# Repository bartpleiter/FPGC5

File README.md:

# FPGC5

My big project, basically started in July 2019 as FPGC3 (versions 1 and 2 do not count). Project exists to learn more about the fundamentals of computers and to improve my Verilog skills, while also designing my own "environment" (PCB, Compilers, OS, etc.) around it.

FPGC is a completely self designed computer, implemented in an EP4CE15 FPGA.

[Project Wiki](https://www.b4rt.nl/fpgc5/) (not fully up to date, but contains a lot of info)

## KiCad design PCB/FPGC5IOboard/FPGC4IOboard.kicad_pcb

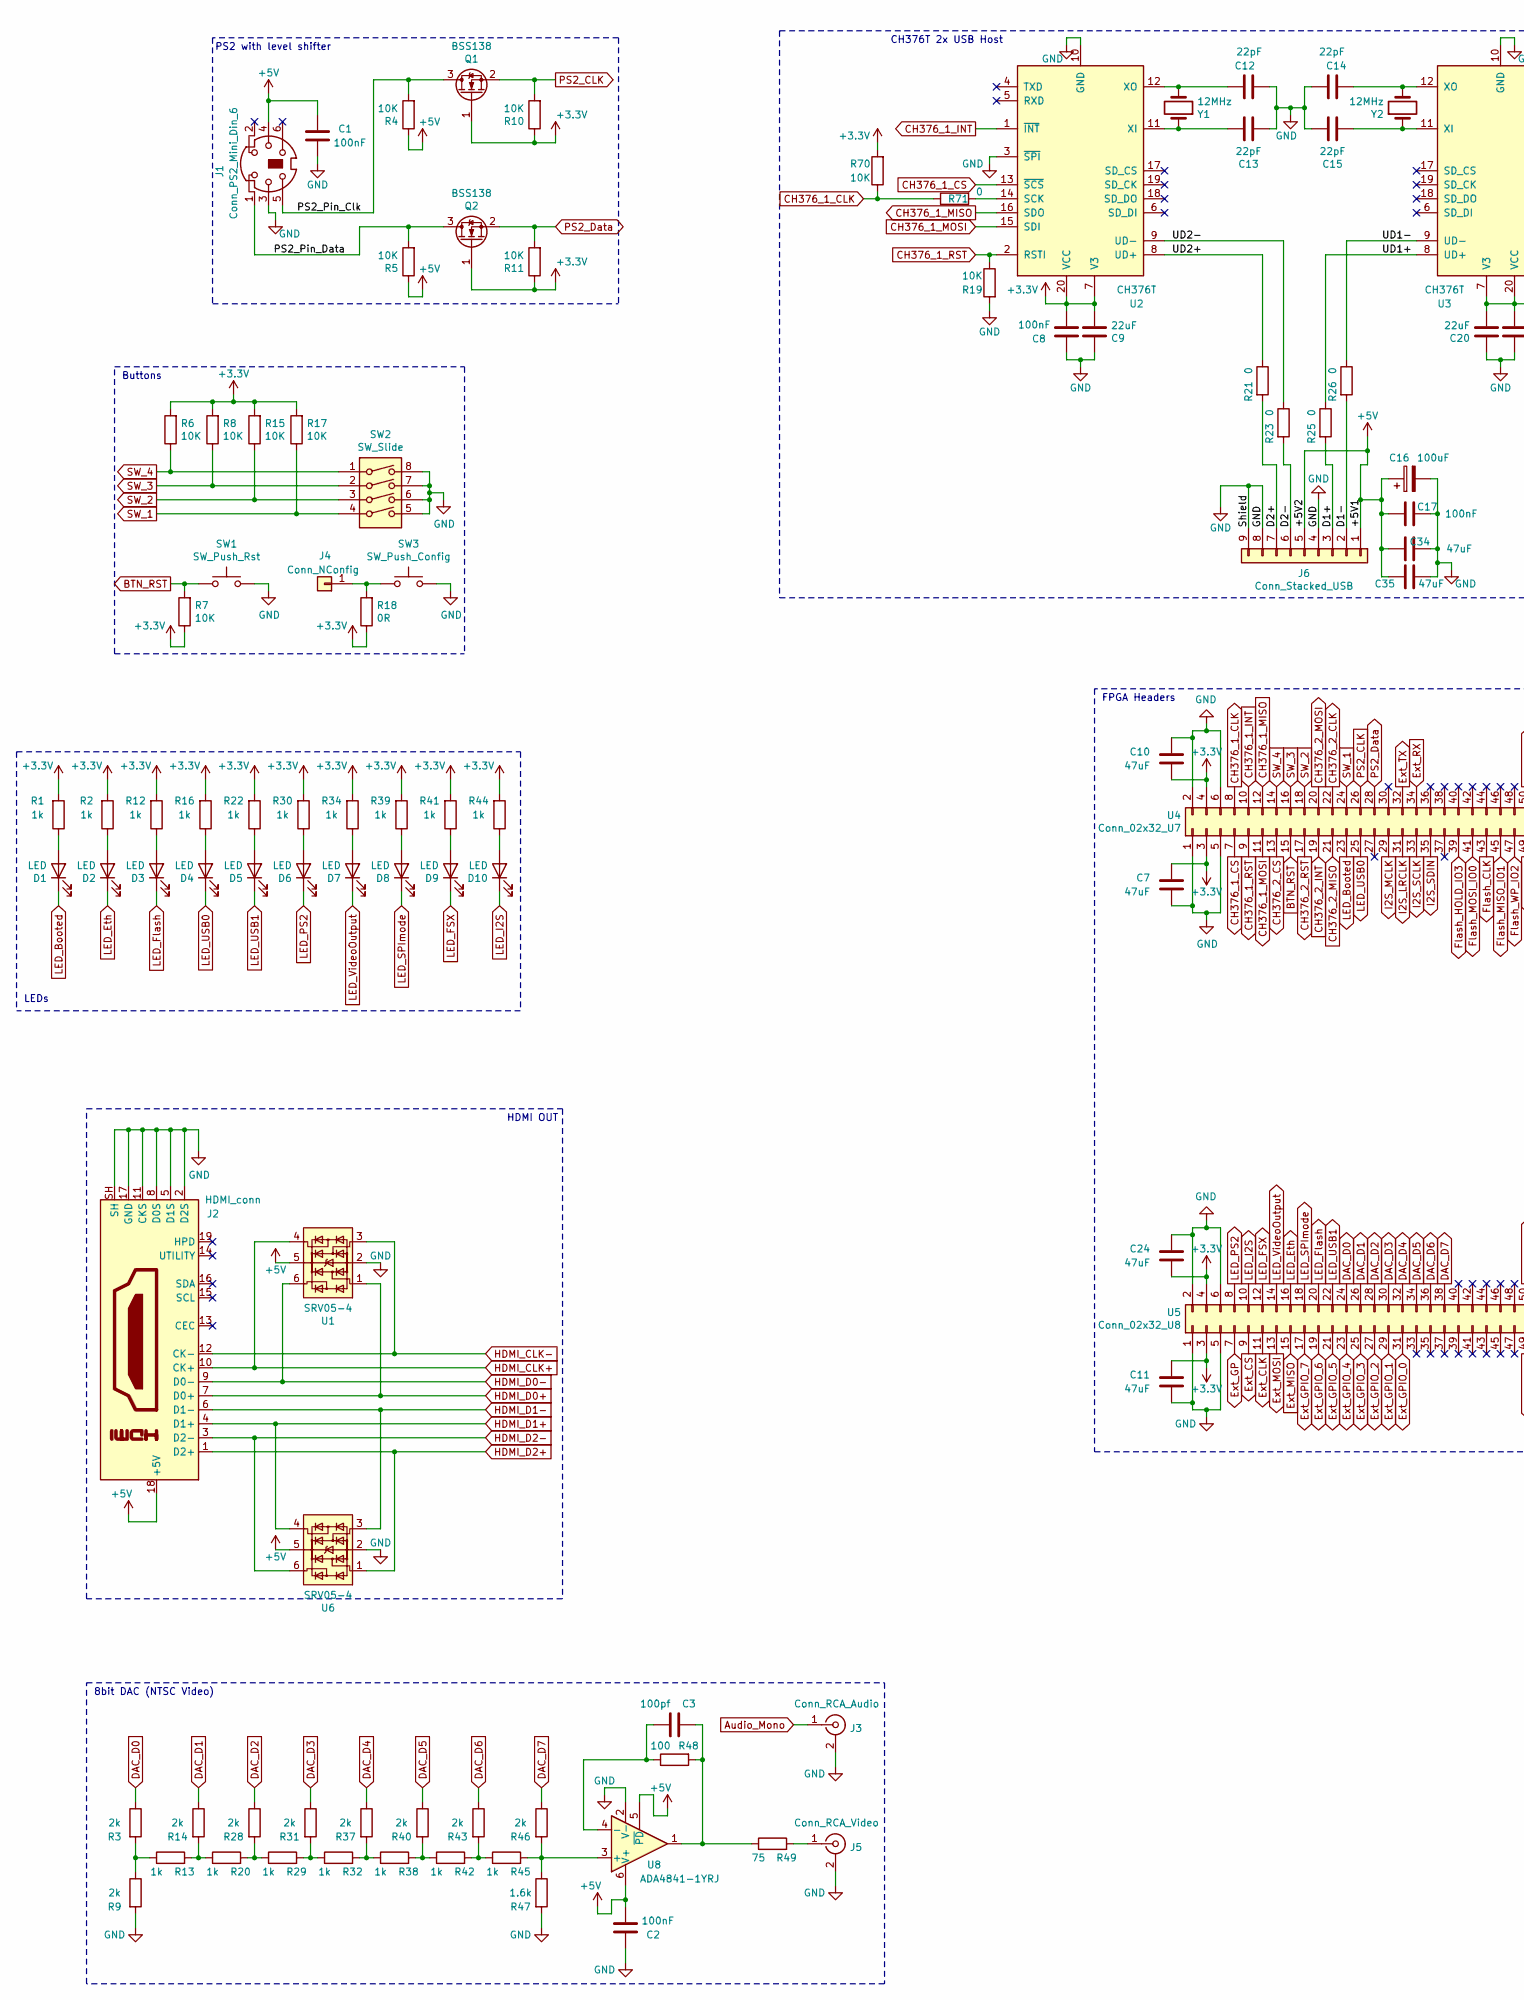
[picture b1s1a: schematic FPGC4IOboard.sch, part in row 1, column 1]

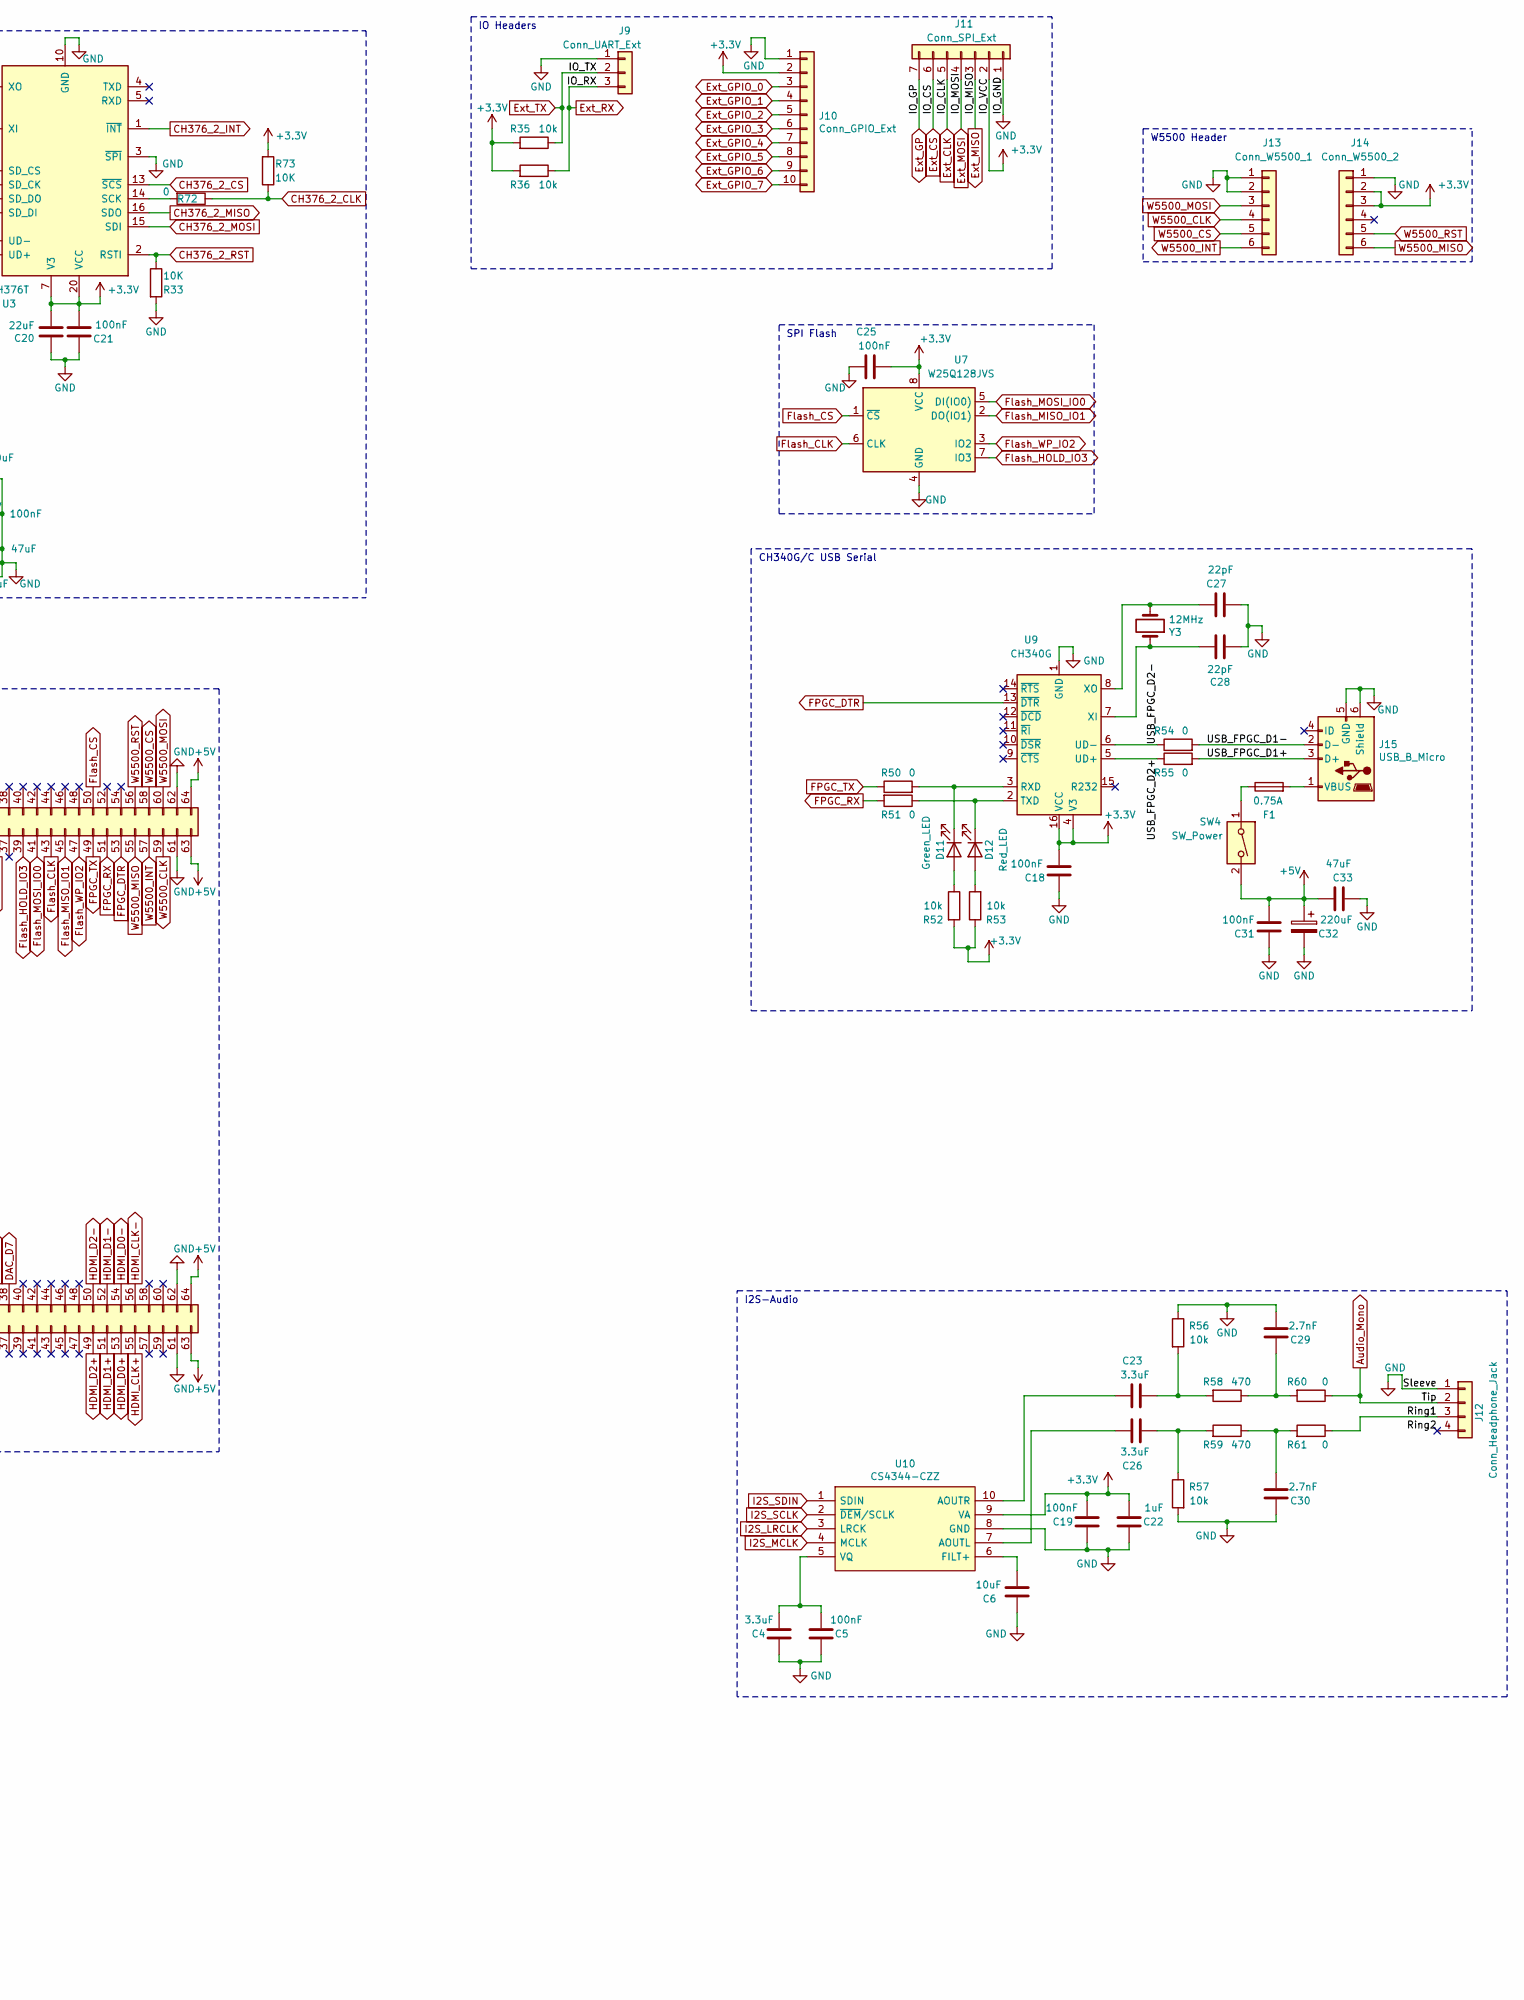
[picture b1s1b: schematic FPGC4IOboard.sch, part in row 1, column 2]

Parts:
C1, C2, C5, C8, C17, C18, C19, C21, C25, C31: 100nF; C_0805_2012Metric_Pad1.18x1.45mm_HandSolder
C3: 100pf; C_0805_2012Metric_Pad1.18x1.45mm_HandSolder
C4, C23, C26: 3.3uF; C_0805_2012Metric_Pad1.18x1.45mm_HandSolder
C6: 10uF; C_0805_2012Metric_Pad1.18x1.45mm_HandSolder
C7, C10, C11, C24, C33, C34, C35: 47uF; C_0805_2012Metric_Pad1.18x1.45mm_HandSolder
C9, C20: 22uF; C_0805_2012Metric_Pad1.18x1.45mm_HandSolder
C12, C13, C14, C15, C27, C28: 22pF; C_0805_2012Metric_Pad1.18x1.45mm_HandSolder
C16: 100uF; CP_Radial_D4.0mm_P2.00mm
C22: 1uF; C_0805_2012Metric_Pad1.18x1.45mm_HandSolder
C29, C30: 2.7nF; C_0805_2012Metric_Pad1.18x1.45mm_HandSolder
C32: 220uF; CP_Radial_D5.0mm_P2.00mm
D1, D2, D3, D4, D5, D6, D7, D8, D9, D10: LED; LED_0805_2012Metric_Pad1.15x1.40mm_HandSolder
D11: Green_LED; LED_0805_2012Metric_Pad1.15x1.40mm_HandSolder
D12: Red_LED; LED_0805_2012Metric_Pad1.15x1.40mm_HandSolder
F1: 0.75A; Fuse_1812
J1: Conn_PS2_Mini_Din_6; PS2
J2: HDMI_conn; HDMI_connector_19
J3: Conn_RCA_Audio; CUI_RCJ-013-Min
J4: Conn_NConfig; PinHeader_1x01_P2.54mm_Vertical
J5: Conn_RCA_Video; CUI_RCJ-013-Min
J6: Conn_Stacked_USB; USB_A_Wuerth_61400826021_Horizontal_Stacked
J9: Conn_UART_Ext; PinSocket_1x03_P2.54mm_Vertical
J10: Conn_GPIO_Ext; PinSocket_1x10_P2.54mm_Vertical
J11: Conn_SPI_Ext; PinSocket_1x07_P2.54mm_Vertical
J12: Conn_Headphone_Jack; TRRS-PJ-320A
J13: Conn_W5500_1; PinSocket_1x06_P2.54mm_Vertical
J14: Conn_W5500_2; PinSocket_1x06_P2.54mm_Vertical
J15: USB_B_Micro; MicroUSB_G30
Q1, Q2: BSS138; SOT-23
R1, R2, R12, R13, R16, R20, R22, R29, R30, R32, R34, R38, R39, R41, R42, R44, R45: 1k; R_0805_2012Metric_Pad1.20x1.40mm_HandSolder
R3, R9, R14, R28, R31, R37, R40, R43, R46: 2k; R_0805_2012Metric_Pad1.20x1.40mm_HandSolder
R4, R5, R6, R7, R8, R10, R11, R15, R17, R19, R33, R70, R73: 10K; R_0805_2012Metric_Pad1.20x1.40mm_HandSolder
R18: 0R; R_0805_2012Metric_Pad1.20x1.40mm_HandSolder
R21, R23, R25, R26, R50, R51, R54, R55, R60, R61, R71, R72: 0; R_0805_2012Metric_Pad1.20x1.40mm_HandSolder
R35, R36, R52, R53, R56, R57: 10k; R_0805_2012Metric_Pad1.20x1.40mm_HandSolder
R47: 1.6k; R_0805_2012Metric_Pad1.20x1.40mm_HandSolder
R48: 100; R_0805_2012Metric_Pad1.20x1.40mm_HandSolder
R49: 75; R_0805_2012Metric_Pad1.20x1.40mm_HandSolder
R58, R59: 470; R_0805_2012Metric_Pad1.20x1.40mm_HandSolder
SW1: SW_Push_Rst; SW_Tactile_SPST_Angled_PTS645Vx39-2LFS
SW2: SW_Slide; SW_DIP_SPSTx04_Slide_6.7x11.72mm_W8.61mm_P2.54mm_LowProfile
SW3: SW_Push_Config; SW_Tactile_SPST_Angled_PTS645Vx39-2LFS
SW4: SW_Power; SS12D06
U1, U6: SRV05-4; SOT-23-6
U2, U3: CH376T; SSOP-20_5.3x7.2mm_P0.65mm
U4: Conn_02x32_U7; PinHeader_2x32_P2.54mm_Vertical
U5: Conn_02x32_U8; PinHeader_2x32_P2.54mm_Vertical
U7: W25Q128JVS; SOIC-8_5.23x5.23mm_P1.27mm
U8: ADA4841-1YRJ; SOT-23-6
U9: CH340G; SOIC-16_3.9x9.9mm_P1.27mm
U10: CS4344-CZZ; SOP50P490X110-10N; Manufacturer_Part_Number CS4344-CZZ; Mouser Part Number 777-CS4344-CZZ
Y1, Y2, Y3: 12MHz; Crystal_HC49-4H_Vertical

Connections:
+3V3: C7.1, C8.2, C9.2, C10.2, C11.1, C18.2, C19.1, C20.2, C21.2, C22.1, C24.2, C25.2, J10.2, J11.2, J14.2, J14.3, Q1.1 (G), Q2.1 (G), R1.2, R2.2, R6.2, R7.1, R8.2, R10.1, R11.1, R12.2, R15.2, R16.2, R17.2, R18.1, R22.2, R30.2, R34.2, R35.2, R36.2, R39.2, R41.2, R44.2, R52.2, R53.1, R70.2, R73.2, U2.7 (V3), U2.20 (VCC), U3.7 (V3), U3.20 (VCC), U4.3, U4.4, U5.3, U5.4, U7.8 (VCC), U9.4 (V3), U9.16 (VCC), U10.9 (VA)
+5V: C1.1, C2.1, C16.1, C17.2, C31.2, C32.1, C33.2, C34.1, C35.1, J1.4, J2.18 (+5V), J6.1, J6.5, R4.1, R5.1, SW4.2, U1.5, U4.63, U4.64, U5.63, U5.64, U6.5, U8.5 (~PD), U8.6 (V+)
/D1+: J6.3, R25.2
/D1-: J6.2, R26.2
/D2+: J6.7, R21.2
/D2-: J6.6, R23.2
/PS2_Pin_Clk: J1.5, Q1.3 (D), R4.2
/PS2_Pin_Data: J1.1, Q2.3 (D), R5.2
/Ring1: J12.3, R61.1
/Ring2: J12.4
/UD1+: R25.1, U3.8 (UD+)
/UD1-: R26.1, U3.9 (UD-)
/UD2+: R21.1, U2.8 (UD+)
/UD2-: R23.1, U2.9 (UD-)
/USB_FPGC_D1+: J15.3 (D+), R55.2
/USB_FPGC_D1-: J15.2 (D-), R54.2
/USB_FPGC_D2+: R55.1, U9.5 (UD+)
/USB_FPGC_D2-: R54.1, U9.6 (UD-)
Audio_Mono: J3.1 (In), J12.2, R60.1
BTN_RST: R7.2, SW1.1, U4.15
CH376_1_CLK: R70.1, R71.1, U4.8
CH376_1_CS: U2.13 (~SCS), U4.7
CH376_1_INT: U2.1 (~INT~), U4.10
CH376_1_MISO: U2.16 (SDO), U4.12
CH376_1_MOSI: U2.15 (SDI), U4.11
CH376_1_RST: R19.1, U2.2 (RSTI), U4.9
CH376_2_CLK: R72.1, R73.1, U4.22
CH376_2_CS: U3.13 (~SCS), U4.13
CH376_2_INT: U3.1 (~INT~), U4.19
CH376_2_MISO: U3.16 (SDO), U4.21
CH376_2_MOSI: U3.15 (SDI), U4.20
CH376_2_RST: R33.1, U3.2 (RSTI), U4.17
DAC_D0: R3.1, U5.24
DAC_D1: R14.1, U5.26
DAC_D2: R28.1, U5.28
DAC_D3: R31.1, U5.30
DAC_D4: R37.1, U5.32
DAC_D5: R40.1, U5.34
DAC_D6: R43.1, U5.36
DAC_D7: R46.1, U5.38
Ext_CLK: J11.5, U5.11
Ext_CS: J11.6, U5.9
Ext_GP: J11.7, U5.7
Ext_GPIO_0: J10.3, U5.31
Ext_GPIO_1: J10.4, U5.29
Ext_GPIO_2: J10.5, U5.27
Ext_GPIO_3: J10.6, U5.25
Ext_GPIO_4: J10.7, U5.23
Ext_GPIO_5: J10.8, U5.21
Ext_GPIO_6: J10.9, U5.19
Ext_GPIO_7: J10.10, U5.17
Ext_MISO: J11.3, U5.15
Ext_MOSI: J11.4, U5.13
Ext_RX: J9.3, R36.1, U4.34
Ext_TX: J9.2, R35.1, U4.32
FPGC_DTR: U4.53, U9.13 (~DTR)
FPGC_RX: R51.2, U4.51
FPGC_TX: R50.1, U4.49
Flash_CLK: U4.43, U7.6 (CLK)
Flash_CS: U4.50, U7.1 (~CS)
Flash_HOLD_IO3: U4.39, U7.7 (IO3)
Flash_MISO_IO1: U4.45, U7.2 (DO(IO1))
Flash_MOSI_IO0: U4.41, U7.5 (DI(IO0))
Flash_WP_IO2: U4.47, U7.3 (IO2)
GND: C1.2, C2.2, C4.2, C5.2, C6.2, C7.2, C8.1, C9.1, C10.1, C11.2, C12.2, C13.1, C14.2, C15.1, C16.2, C17.1, C18.1, C19.2, C20.1, C21.1, C22.2, C24.1, C25.1, C27.2, C28.1, C29.1, C30.2, C31.1, C32.2, C33.1, C34.2, C35.2, J1.3, J2.2 (D2S), J2.5 (D1S), J2.8 (D0S), J2.11 (CKS), J2.17 (GND), J2.SH, J3.2 (Ext), J5.2 (Ext), J6.4, J6.8, J6.9, J9.1, J10.1, J11.1, J12.1, J13.1, J13.2, J14.1, J15.5 (GND), J15.6 (Shield), R9.2, R19.2, R33.2, R47.2, R56.1, R57.2, SW1.2, SW2.5, SW2.6, SW2.7, SW2.8, SW3.2, SW4.4, U1.2, U2.3 (~SPI~), U2.10 (GND), U3.3 (~SPI~), U3.10 (GND), U4.1, U4.2, U4.5, U4.6, U4.61, U4.62, U5.1, U5.2, U5.5, U5.6, U5.61, U5.62, U6.2, U7.4 (GND), U8.2 (V-), U9.1 (GND), U10.8 (GND)
HDMI_CLK+: J2.10 (CK+), U1.4, U5.55
HDMI_CLK-: J2.12 (CK-), U1.3, U5.56
HDMI_D0+: J2.7 (D0+), U1.1, U5.53
HDMI_D0-: J2.9 (D0-), U1.6, U5.54
HDMI_D1+: J2.4 (D1+), U5.51, U6.4
HDMI_D1-: J2.6 (D1-), U5.52, U6.3
HDMI_D2+: J2.1 (D2+), U5.49, U6.1
HDMI_D2-: J2.3 (D2-), U5.50, U6.6
I2S_LRCLK: U4.31, U10.3 (LRCK)
I2S_MCLK: U4.29, U10.4 (MCLK)
I2S_SCLK: U4.33, U10.2 (~DEM~/SCLK)
I2S_SDIN: U4.35, U10.1 (SDIN)
LED_Booted: D1.1 (K), U4.23
LED_Eth: D2.1 (K), U5.16
LED_FSX: D9.1 (K), U5.12
LED_Flash: D3.1 (K), U5.20
LED_I2S: D10.1 (K), U5.10
LED_PS2: D6.1 (K), U5.8
LED_SPImode: D8.1 (K), U5.18
LED_USB0: D4.1 (K), U4.25
LED_USB1: D5.1 (K), U5.22
LED_VideoOutput: D7.1 (K), U5.14
unnamed: C3.1, R48.2, R49.1, U8.1
unnamed: C3.2, R48.1, U8.4 (-)
unnamed: C4.1, C5.1, U10.5 (VQ)
unnamed: C6.1, U10.6 (FILT+)
unnamed: C12.1, U2.12 (XO), Y1.2
unnamed: C13.2, U2.11 (XI), Y1.1
unnamed: C14.1, U3.12 (XO), Y2.2
unnamed: C15.2, U3.11 (XI), Y2.1
unnamed: C23.1, U10.10 (AOUTR)
unnamed: C23.2, R56.2, R58.2
unnamed: C26.1, U10.7 (AOUTL)
unnamed: C26.2, R57.1, R59.2
unnamed: C27.1, U9.8 (XO), Y3.2
unnamed: C28.2, U9.7 (XI), Y3.1
unnamed: C29.2, R58.1, R60.2
unnamed: C30.1, R59.1, R61.2
unnamed: D1.2 (A), R1.1
unnamed: D2.2 (A), R2.1
unnamed: D3.2 (A), R12.1
unnamed: D4.2 (A), R16.1
unnamed: D5.2 (A), R22.1
unnamed: D6.2 (A), R30.1
unnamed: D7.2 (A), R34.1
unnamed: D8.2 (A), R39.1
unnamed: D9.2 (A), R41.1
unnamed: D10.2 (A), R44.1
unnamed: D11.1 (K), R50.2, U9.3 (RXD)
unnamed: D11.2 (A), R52.1
unnamed: D12.1 (K), R51.1, U9.2 (TXD)
unnamed: D12.2 (A), R53.2
unnamed: F1.1, SW4.1
unnamed: F1.2, J15.1 (VBUS)
unnamed: J4.1, R18.2, SW3.1
unnamed: J5.1 (In), R49.2
unnamed: R3.2, R9.1, R13.1
unnamed: R13.2, R14.2, R20.1
unnamed: R20.2, R28.2, R29.1
unnamed: R29.2, R31.2, R32.1
unnamed: R32.2, R37.2, R38.1
unnamed: R38.2, R40.2, R42.1
unnamed: R42.2, R43.2, R45.1
unnamed: R45.2, R46.2, R47.1, U8.3 (+)
unnamed: R71.2, U2.14 (SCK)
unnamed: R72.2, U3.14 (SCK)
PS2_CLK: Q1.2 (S), R10.2, U4.26
PS2_Data: Q2.2 (S), R11.2, U4.28
SW_1: R17.1, SW2.4, U4.24
SW_2: R15.1, SW2.3, U4.18
SW_3: R8.1, SW2.2, U4.16
SW_4: R6.1, SW2.1, U4.14
W5500_CLK: J13.4, U4.59
W5500_CS: J13.5, U4.58
W5500_INT: J13.6, U4.57
W5500_MISO: J14.6, U4.55
W5500_MOSI: J13.3, U4.60
W5500_RST: J14.5, U4.56

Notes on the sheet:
CH340G/C USB Serial
IO Headers
PS2 with level shifter
CH376T 2x USB Host
I2S-Audio
SPI Flash
W5500 Header
Buttons
FPGA Headers
LEDs
HDMI OUT
8bit DAC (NTSC Video)

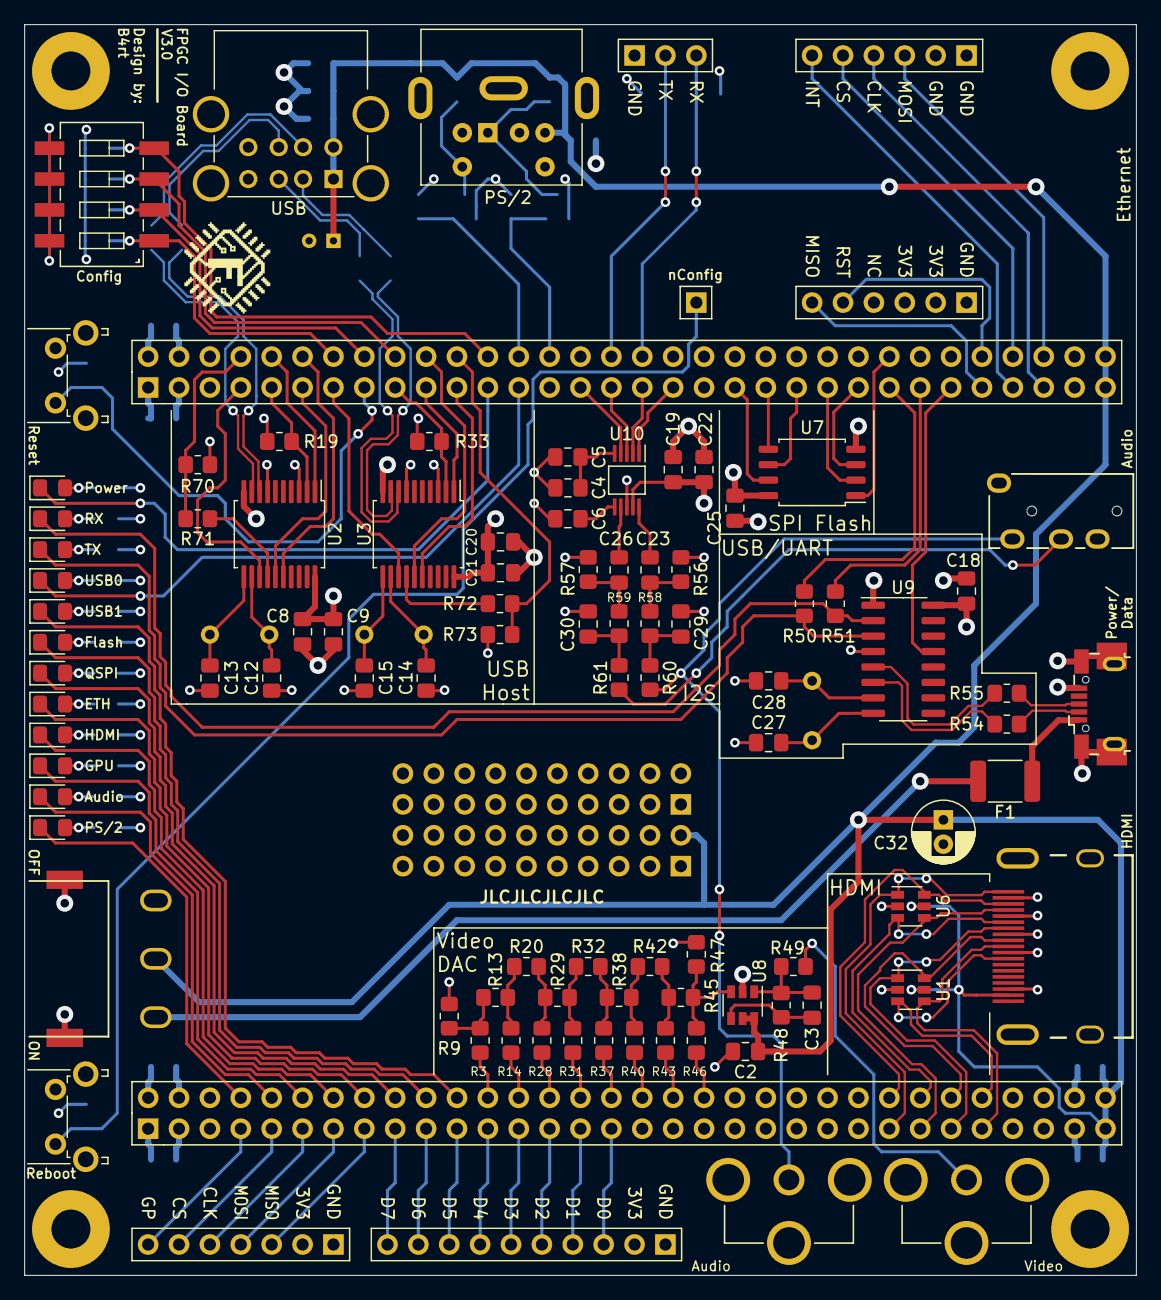
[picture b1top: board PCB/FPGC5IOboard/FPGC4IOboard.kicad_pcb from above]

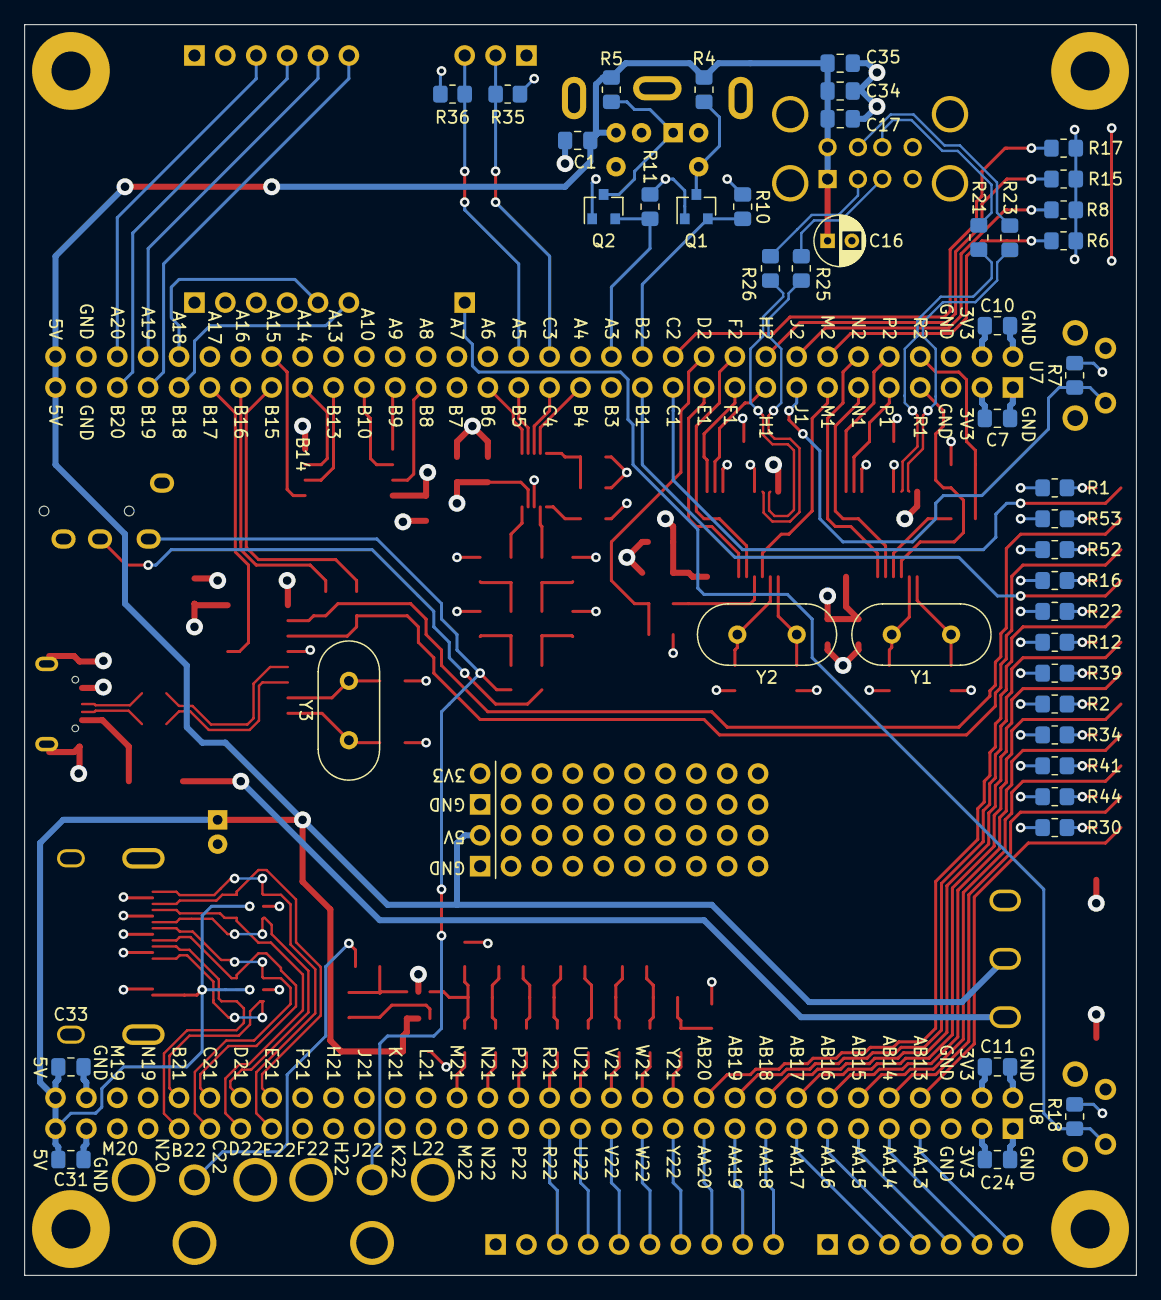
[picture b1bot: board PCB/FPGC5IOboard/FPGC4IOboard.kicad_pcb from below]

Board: 4 copper layers, 91.4 x 102.9 mm, 144 parts (44 on the bottom side), 142 nets.

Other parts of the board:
LOGO: LOGO

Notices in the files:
Quartus/FPGC4.qsf:
Copyright (C) 1991-2012 Altera Corporation
